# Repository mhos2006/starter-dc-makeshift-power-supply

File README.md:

# 5V Linear Breadboard Power Supply

## Overview
A stable, heavily filtered 5V DC power supply built on a breadboard, designed to step down a raw 9.6V NiMH battery pack. This module serves as the foundational power grid for all subsequent digital logic and microcontroller projects. 

## Hardware Specifications
* **Input Voltage:** 9.6V DC (8x AA NiMH cells in series)
* **Output Voltage:** 5.0V DC 
* **Core Regulator:** STMicroelectronics L7805CV (with TO-220 aluminum heatsink for thermal dissipation)
* **Reverse Polarity Protection:** 1N4007 Diode on the input rail.
* **Filtering:**
  * Input Buffer: 100µF Electrolytic Capacitor (smooths battery sag)
  * Output Filter: 10µF Electrolytic Capacitor (suppresses logic switching ripple)
* **Status Indicator:** 5mm Red LED driven by a 1kΩ current-limiting resistor.

## Schematic

## Testing & Verification
* Open-circuit input voltage verified at ~9.6V via digital multimeter.
* Regulated output voltage verified at a stable 5.0V under no-load and light-load conditions.
* Continuity testing performed to ensure complete electrical isolation between the L7805 thermal tab and the aluminum heatsink.

## Breadboard layout

## Schematic and PCB Documentation

I created the schematic using KiCad software. While my schematic has been verified, I have moved the components over to PCB software. PCB layout and component placement is in progress.

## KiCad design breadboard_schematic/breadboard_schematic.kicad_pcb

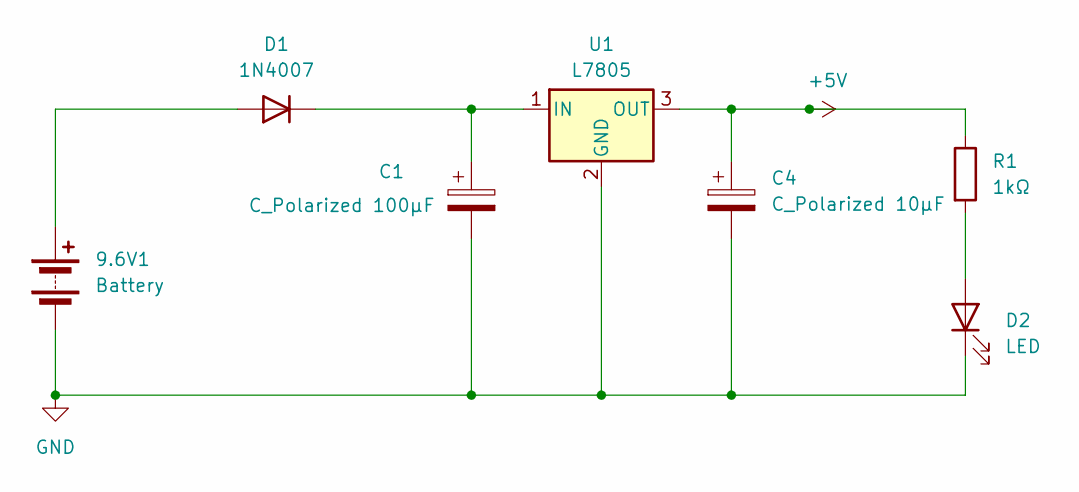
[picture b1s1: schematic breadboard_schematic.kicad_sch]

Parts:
9.6V1: Battery; PinHeader_1x02_P2.54mm_Vertical
C1: C_Polarized 100μF; CP_Radial_D5.0mm_P2.00mm
C4: C_Polarized 10μF; CP_Radial_D5.0mm_P2.00mm
D1: 1N4007; D_DO-41_SOD81_P10.16mm_Horizontal
D2: LED; LED_D5.0mm
R1: 1kΩ; R_Axial_DIN0207_L6.3mm_D2.5mm_P10.16mm_Horizontal
U1: L7805; TO-220-3_Vertical

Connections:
+5V: C4.1, R1.1, U1.3 (OUT)
GND: 9.6V1.2 (-), C1.2, C4.2, D2.1 (K), U1.2 (GND)
unnamed: 9.6V1.1 (+), D1.2 (A)
unnamed: C1.1, D1.1 (K), U1.1 (IN)
unnamed: D2.2 (A), R1.2

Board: 2 copper layers, 7 parts (0 on the bottom side), 5 nets, no tracks yet.
